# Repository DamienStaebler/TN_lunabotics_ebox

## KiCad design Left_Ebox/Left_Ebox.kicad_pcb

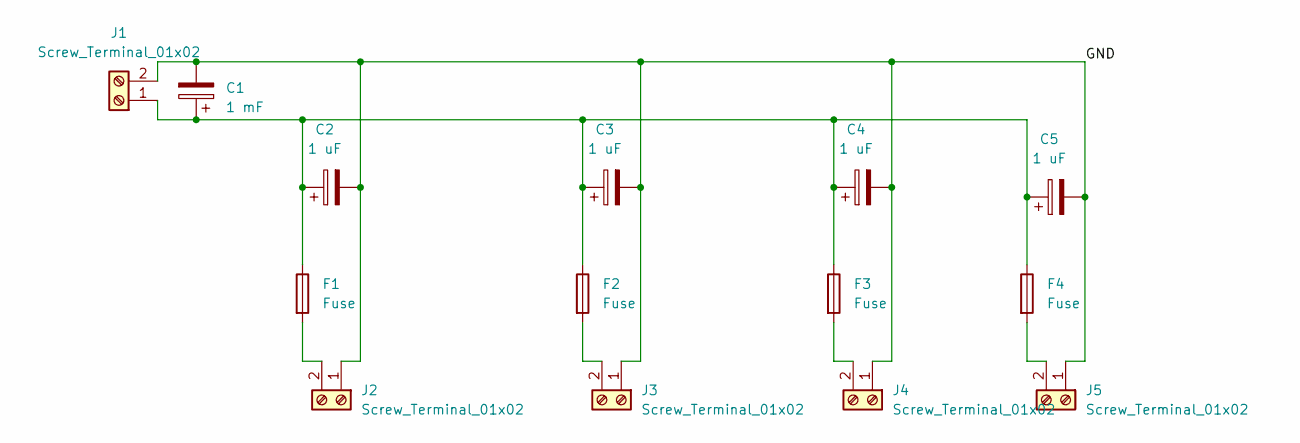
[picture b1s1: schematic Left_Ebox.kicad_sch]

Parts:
C1: 1 mF; CP_Radial_D8.0mm_P3.80mm
C2, C3, C4, C5: 1 uF; CP_Radial_D5.0mm_P2.50mm
F1, F2, F3, F4: Fuse; FUSE
J1, J5: Screw_Terminal_01x02; BATTERY_AND_LOW_VOLTAGE_CONNECTOR
J2, J3, J4: Screw_Terminal_01x02; SPARMAX_CONN

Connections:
/GND: C1.2, C2.2, C3.2, C4.2, C5.2, J1.2, J2.1, J3.1, J4.1, J5.1
unnamed: C1.1, C2.1, C3.1, C4.1, C5.1, F1.1, F2.1, F3.1, F4.1, J1.1
unnamed: F1.2, J2.2
unnamed: F2.2, J3.2
unnamed: F3.2, J4.2
unnamed: F4.2, J5.2

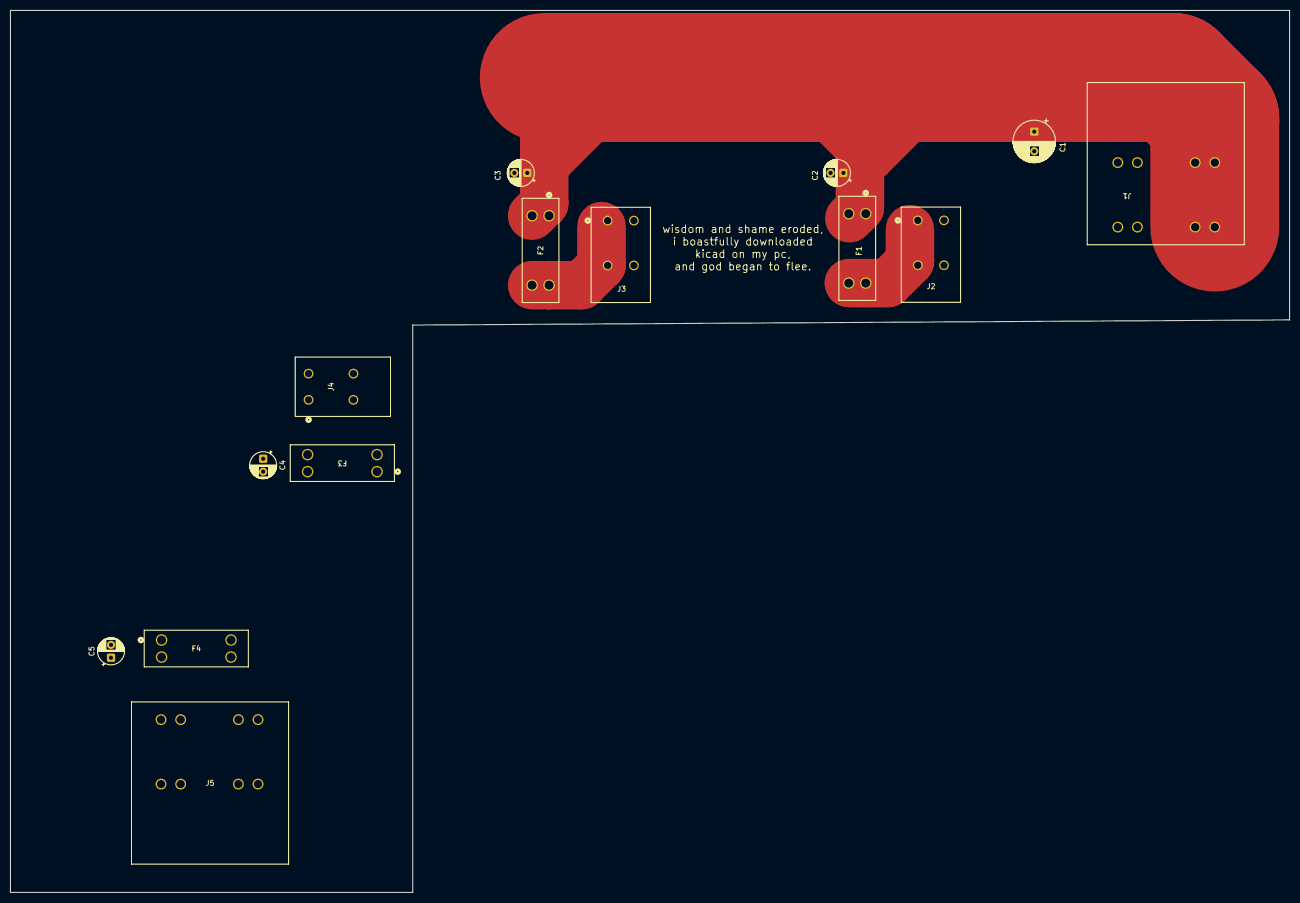
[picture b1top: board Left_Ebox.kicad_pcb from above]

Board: 2 copper layers, 248.0 x 171.0 mm, 14 parts (0 on the bottom side), 6 nets.
